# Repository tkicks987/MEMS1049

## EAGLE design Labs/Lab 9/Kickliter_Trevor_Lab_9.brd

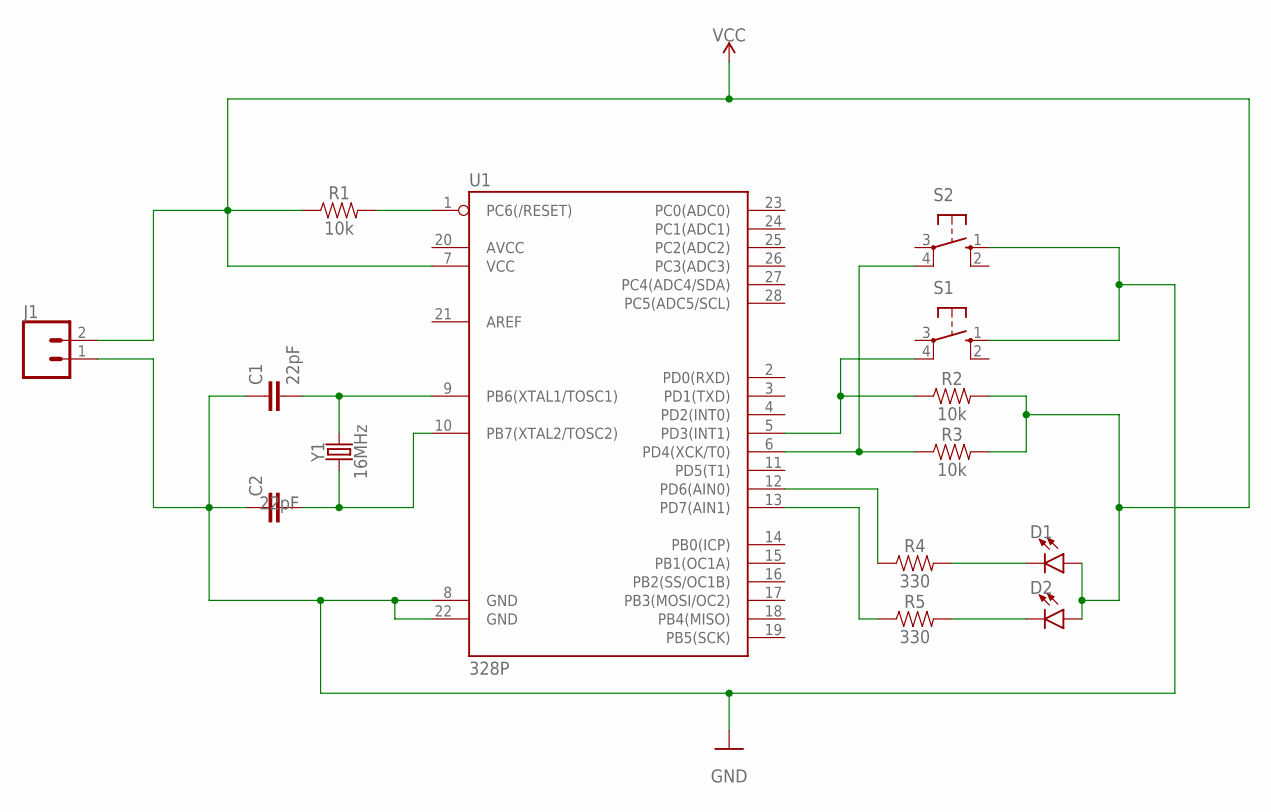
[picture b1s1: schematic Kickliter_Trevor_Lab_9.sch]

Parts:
C1, C2: 22pF; CAP-PTH-2.54
D1, D2: LED-3MM-NO_SILK; LED_3MM-NS
J1: CONN_02; 1X02
R1, R2, R3: 10k; AXIAL-0.3
R4, R5: 330; AXIAL-0.3
S1, S2: 10-XX; B3F-10XX
U1: 328P; DIP28
Y1: 16MHz; HC49US

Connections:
GND: C1.1, C2.1, J1.1, S1.1 (S), S2.1 (S), U1.8 (GND), U1.22 (GND)
unnamed: R1.P$2 (2), U1.1 (PC6(/RESET))
unnamed: C1.2, U1.9 (PB6(XTAL1/TOSC1)), Y1.2
unnamed: R4.P$1 (1), U1.12 (PD6(AIN0))
unnamed: C2.2, U1.10 (PB7(XTAL2/TOSC2)), Y1.1
unnamed: D1.K (C), R4.P$2 (2)
unnamed: R5.P$1 (1), U1.13 (PD7(AIN1))
unnamed: D2.K (C), R5.P$2 (2)
unnamed: R2.P$1 (1), S1.4 (P1), U1.5 (PD3(INT1))
unnamed: R3.P$1 (1), S2.4 (P1), U1.6 (PD4(XCK/T0))
VCC: D1.A, D2.A, J1.2, R1.P$1 (1), R2.P$2 (2), R3.P$2 (2), U1.7 (VCC)

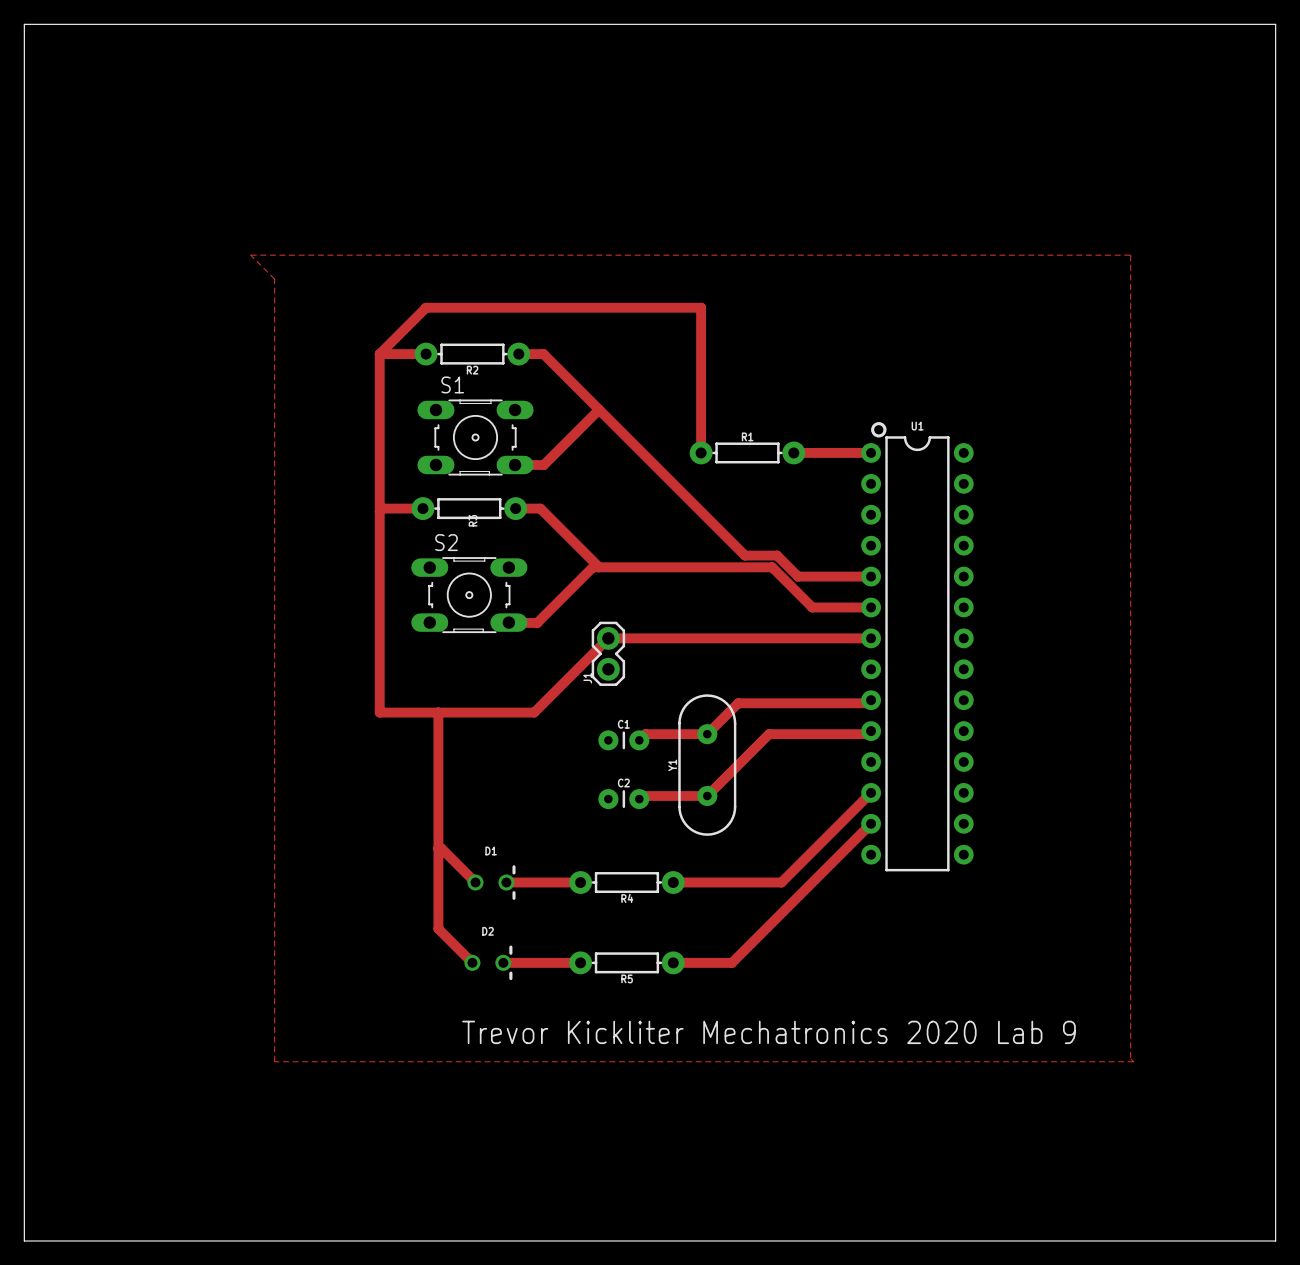
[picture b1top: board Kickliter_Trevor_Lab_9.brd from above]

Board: 2 copper layers, 102.8 x 100.0 mm, 14 parts (0 on the bottom side), 11 nets.

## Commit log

2020-03-30 2nd commit
2020-03-30 Added labs
2020-03-30 whoops
2020-04-03 Added lab 8 - interrupt in assembly
2020-04-07 Fixed Lab 7 code
2020-04-13 Added Lab 9 - intro to PCBs

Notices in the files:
parts and their libraries:
SparkFun-Capacitors: Licensing: Creative Commons ShareAlike 4.0 International - https://creativecommons.org/licenses/by-sa/4.0
